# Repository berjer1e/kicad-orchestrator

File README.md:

# KiCad Orchestrator — 100% AI-Generated Hardware Design & Verification Suite

> [!IMPORTANT]
> **🇺🇦 Повністю згенерований ШІ-інструмент / 🇬🇧 100% AI-Generated Tool**
>
> **Українською:** Весь цей репозиторій — **14-інструментний MCP-сервер для KiCad 10**, **5-агентний оркестратор-плагін (`v0.5.0`)** (разом із Design QA Gate та Gemini API делегатором) та **приклад проєкту друкованої плати калькулятора (`examples/calculator/`)** — є **повністю згенерованим ШІ інструментом (100% AI-Generated Hardware Design & Verification Suite)**. Перед виготовленням серійних плат обов'язково переглядайте Gerber, drill-файли та DRC-звіти.
>
> **English:** This entire repository — the **14-tool KiCad 10 MCP server**, the **5-agent orchestrator plugin (`v0.5.0`)**, and the **Calculator PCB reference project (`examples/calculator/`)** — is a **100% AI-Generated Tool**. Always review exported Gerbers, drill maps, and DRC reports prior to mass fabrication.

---

## Showcase: Calculator Reference Project (`examples/calculator/`)

The flagship hardware project in [`./examples/calculator/`](./examples/calculator/) is a complete KiCad 10 rechargeable desktop calculator board featuring:

- **MCU & Core:** `ATmega328P-AU` + `16 MHz` (`HC-49S`) crystal oscillator with `22 pF` load capacitors and `100 nF` decoupling
- **Display Mezzanine:** `LCD1602 I2C` interface (`J_LCD1` `JST-XH` / header architecture with mechanical & Z-clearance audit)
- **User Input:** `32-key 4x8` tactile switch matrix (`SW1..SW32`, `6x6 mm`) with `1N4148` anti-ghosting diodes (`D1..D32`)
- **Power & Charging:** `HW-373 TP4056` Li-ion USB Type-C charger (`U_CHG1`, `2.0 mm` edge overhang) + `MT3608` boost converter (`U_BOOST1`) + `J_BATT1` / `J_PWR_IN1` / `J_SW_PWR1` `JST-XH` connectors
- **PCB Stackup & Routing:** `130 x 90 mm` 2-layer `FR-4` (`1.6 mm`), explicit `GND` tracks + `B.Cu` ground zone pour (`Доріжки + Зона`), and `M3` (`H1..H4`) corner mounting holes

### 3D Top Render & 2D Copper/Zone Preview

| 3D Top View (`calculator_top.png`) | Multi-Layer SVG Preview (`calculator_preview.svg`) |
| :---: | :---: |
|  |  |

Full automated verification output for the Calculator board is saved in [`./examples/calculator/output/audit_report.json`](./examples/calculator/output/audit_report.json).

---

## Repository Structure

```text
kicad-orchestrator/
├── mcp_server/                 # FastMCP server + S-expression PCB inspector + editor + generators
│   ├── server.py               # 20 consolidated FastMCP tools + compact schema sync helper
│   ├── run_tool.py             # Direct CLI dispatcher, `--sync-schemas`, and `--save-state-summary`
│   ├── api_delegate.py         # Gemini Interactions & Antigravity SDK delegator (`gemini-3.5-flash-lite` .. `gemini-4-carbon`)
│   ├── cli_wrapper.py          # KiCad 10 `kicad-cli.exe` wrapper with isolated config & lock-safe staging
│   ├── pcb_inspector.py        # Balanced-paren S-expr parser, compact audit mode, IPC-2221, mezzanine & QA gate
│   ├── pcb_editor.py           # Safe S-expr layout editor, trace/via mutator & 2-layer A* autorouter
│   ├── requirements.txt        # Python dependencies (`mcp`, `pydantic`, `google-genai`, `google-antigravity`)
│   ├── generators/             # BOM parser & KiCad 10 footprint/symbol generators
│   │   ├── __init__.py
│   │   ├── bom_parser.py
│   │   ├── footprint_gen.py
│   │   ├── symbol_gen.py
│   │   └── templates.py
│   └── schemas/                # 14 exported compact JSON tool schemas (`parameters.type == "object"`)
├── plugin/                     # Antigravity plugin bundle (`v0.5.0`)
│   ├── plugin.json
│   ├── mcp_config.json
│   ├── assets/logo.svg
│   └── skills/
│       ├── kicad-orchestrator/SKILL.md
│       ├── kicad-searcher/SKILL.md
│       ├── kicad-generator/SKILL.md
│       ├── kicad-tracer/SKILL.md
│       └── kicad-tester-converter/SKILL.md
├── examples/calculator/        # Complete Calculator KiCad 10 project + `Items.DOCX` + exports
├── LICENSE                     # MIT License (Copyright 2026 berjer1e)
└── README.md
```

---

## Architecture: 14 Consolidated MCP Tools (`v0.5.0`)

All 20 consolidated tools are exposed via FastMCP (`mcp_server/server.py`) with compact 1-sentence schema descriptions (`mcp_server/schemas/*.json`), compact/failures-first inspection defaults (`inspect_pcb_layout(compact=True)`), one-shot disk caching (`run_tool.py --save-state-summary`), deterministic schematic/netlist/PCB generation (`create_schematic`, `run_electrical_pipeline`), electrical netlist preparation (`create_netlist_from_bom`, `apply_netlist_to_pcb`, `add_nets_to_pcb`, `assign_pad_nets`), and optional Gemini SDK subtask delegation (`mcp_server/api_delegate.py`).

### 0. Safe S-Expression PCB Editing & 2-Layer A* Autorouting (`pcb_editor.py`)
| Tool | Key Parameters | Purpose |
| :--- | :--- | :--- |
| `edit_pcb_layout` | `pcb_path`, `board_outline=None`, `footprint_placements=None`, `zones=None`, `output_path=None` | Safely updates `Edge.Cuts` (rectangular or rounded corners), moves/rotates footprints by reference designator, and creates copper `(zone ...)` blocks without `pcbnew` SWIG/wxWidgets assertions. |
| `edit_pcb_traces` | `pcb_path`, `add_segments=None`, `add_vias=None`, `clear_nets=None`, `clear_bbox=None`, `output_path=None` | Adds or clears copper `(segment ...)` and `(via ...)` items with validated integer net IDs (resolving human net names automatically so `kicad-cli` never hangs on string net names). |
| `autoroute_pcb_nets` | `pcb_path`, `nets=None`, `grid_step_mm=0.5`, `trace_width_mm=0.3`, `clearance_mm=0.25`, `allow_vias=True`, `output_path=None` | Built-in obstacle-aware 2-layer 45°/orthogonal A* grid router directly over `.kicad_pcb` S-expressions for unrouted nets. |

### 1. S-Expression PCB Inspection & IPC-2221 Audit
| Tool | Key Parameters | Purpose |
| :--- | :--- | :--- |
| `inspect_pcb_layout` | `pcb_path` | Parses `Edge.Cuts` bounds, `board_stackup`, `silkscreen_audit` (font sizes, pad overlaps, connector pin labels), footprint bboxes, `estimated_height_mm`, track/via/zone stats, and lock status. |
| `find_unrouted_pads` | `pcb_path`, `net_filter=None`, `tolerance_mm=0.05` | Detects pads on multi-pad nets missing explicit copper `segment` tracks, separating `zone_only_pads` (e.g. `GND` relying only on zone pours) from `completely_unrouted_pads`. |
| `analyze_pcb_traces` | `pcb_path`, `net_currents_a=None`, `copper_oz=1.0`, `max_temp_rise_c=10.0`, `max_voltage_drop_v=0.1`, `neckdown_max_length_mm=3.0` | Computes IPC-2221 minimum trace widths, classifies pad-entry neck-downs (`trunk_ok`, `valid_neckdown`, `undersized_segment`), calculates segment resistance & `ΔU = I·R`, and audits critical net lengths (crystal `<= 15 mm`, `100 nF` decoupling `<= 8 mm`, `I2C`). |
| `manage_design_decisions` | `project_dir`, `action="check"`, `decisions=None`, `bom_or_pcb_path=None` | Checks, loads, or saves `<project_dir>/design_decisions.json` across the 8 Step 1.5 Design QA Gate categories. |

### 2. Mezzanine & 3D Mechanical Fit
| Tool | Key Parameters | Purpose |
| :--- | :--- | :--- |
| `check_mechanical_fit` | `pcb_path`, `min_clearance_mm=0.5`, `connector_clearance_mm=2.0`, `standoff_keepout_dia_mm=6.5`, `standoff_height_mm=10.0`, `mezzanine_modules=None` | Runs Checks A–E: same-side courtyard collisions, edge overhangs, connector mating clearances (`>= 2.0 mm`), mounting hole & display notes, standoff/screw-head keepouts (`M2.5 >= 5.5 mm`, `M3 >= 6.5 mm`), 2D projection + 3D Z-clearance (`estimated_height_mm`), and rigid board-to-board header alignment. |

### 3. Lock-Safe Zone Refill & DRC / ERC
| Tool | Key Parameters | Purpose |
| :--- | :--- | :--- |
| `refill_pcb_zones` | `pcb_path`, `output_path=None`, `force_when_locked=False` | Refills copper zones via `kicad-cli` in-place, or stages to `output_path` / `<stem>_refilled.kicad_pcb` when locked. |
| `run_validations` | `target_path=""`, `validation_type="drc"`, `output_path=None`, `schematic_parity=True`, `refill_zones=True`, `save_board=False` | Consolidated validation entrypoint (`drc` with `--schematic-parity`, `erc`, `footprint`/`symbol` SVG check, `locks` check, or `version`). |

### 4. Module Footprint/Symbol Generators & BOM Parser
| Tool | Key Parameters | Purpose |
| :--- | :--- | :--- |
| `parse_bom` | `source` | Parses Ukrainian/English BOM specs (`.txt`, `.csv`, or prose extracted from `.docx` such as `Items.DOCX`) into components, `board_properties`, `connector_details` (orientation, mounting, pitch, keying, current rating), pinouts, and rules. |
| `list_modules` | *(none)* | Lists built-in parametric module templates (`Mini360`, `Mini560`, `MT3608`, `TP4056_HW373`) and supported overrides. |
| `generate_module` | `module_name`, `output_dir`, `kind="both"`, `overrides=None` | Generates KiCad 10 `.kicad_mod` (`version 20260206`) footprints and/or `.kicad_sym` (`version 20251024`) symbols with keepouts and 100-mil pins. |

### 5. Manufacturing Exports & Environment
| Tool | Key Parameters | Purpose |
| :--- | :--- | :--- |
| `export_project` | `target_path`, `output_path`, `export_type="pcb_svg"`, `layers=None`, `width=1600`, `height=900`, `side="top"`, `quality="basic"`, `refill_zones=True` | Consolidated export tool supporting `gerbers`, `drill`, `step`, `sch_pdf`, `pcb_svg`, and `3d` PNG/JPEG renders (auto-stages zone refill if locked). |

---

## Architecture: 5 Autonomous Agent Skills & Step 1.5 Design QA Gate

The [`plugin/`](./plugin/) bundle (`v0.3.0`) coordinates five specialized agents:

1. **`kicad-orchestrator`** — Master coordinator executing the 6-stage pipeline:
   - **Step 1 (Ingest & Pre-Flight):** Runs `parse_bom` (`board_properties`, `connector_details`), `run_validations(..., validation_type="locks")`, and caches compact PCB state (`--save-state-summary`) to `output/state_summary.json`.
   - **Step 1.5 (Design QA Gate):** Calls `manage_design_decisions(project_dir, action="check")` and interactively resolves any ambiguities with the user via `ask_question` / `/grill-me`, persisting answers into `<project_dir>/design_decisions.json` across **8 mandatory categories**:
     1. `display_mounting_mode` (`panel_cable` vs `pcb_mezzanine`)
     2. `module_variants` (e.g. `Mini560` SMD `15x18` vs THT `29x18`)
     3. `connector_orientation_and_keying` (`vertical` vs `right_angle`, `keyed` vs unkeyed)
     4. `button_interface` (on-board `6x6` tactile switches vs external panel buttons)
     5. `pcb_stackup_and_limits` (`layer_count`, `copper_oz` `1.0`/`2.0`, `board_thickness_mm`)
     6. `board_shape_and_mounting` (`M2.5`/`M3` holes, `5.5`/`6.5 mm` standoff keepouts, `R3` corners)
     7. `silkscreen_conventions` (functional designators like `U_CHG1`, pin/polarity labels)
     8. `enclosure_fit_and_overhangs` (USB Type-C overhang, max component Z-height)
   - **Step 2 (Discovery & Generation):** Dispatches `searcher` and `generator`.
   - **Step 3 (Routing & Mechanical Audit):** Dispatches `tracer`.
   - **Step 4 (Verification & Export):** Dispatches `tester-converter`.
   - **Step 5 (Final Report):** Summarizes verified artifacts, metrics, and warnings.
2. **`kicad-searcher`** — Verifies KiCad 10 standard library mappings, module dimensions, connector orientation/mounting/pitch/keying, 3D Z-heights (`estimated_height_mm`), and mezzanine `(dx, dy)` hole-to-header offsets.
3. **`kicad-generator`** — Loads `design_decisions.json`, consumes `board_properties` & `connector_details`, and builds `.kicad_mod`/`.kicad_sym` files with standoff keepouts, keyed pin-1 markers, and `>= 1.0 x 0.15 mm` silkscreen labels.
4. **`kicad-tracer`** — Enforces IPC-2221 trace widths with pad-aware neck-down (`<= 3.0 mm`) & `ΔU = I·R <= 0.1 V`, explicit `GND` tracks + copper zone ("Доріжки + Зона"), silkscreen polarity traceability, and the 3 stacked/mezzanine checks.
5. **`kicad-tester-converter`** — Runs the full verification and export suite (`run_validations` for `locks`/`erc`/`drc`, `inspect_pcb_layout`, `analyze_pcb_traces`, `find_unrouted_pads`, `check_mechanical_fit`, `refill_pcb_zones`, and `export_project` for Gerber/Drill/STEP/SVG/PDF/3D outputs).

---

## Quick Start (Windows / KiCad 10)

### 1. Prerequisites
- **KiCad 10.0+** installed (the `kicad-cli` executable available on your PATH)
- **Python 3.11+**

### Host Integration

The repository is split into a client-independent MCP backend and host-specific prompt
adapters. Read [`AGENTS.md`](./AGENTS.md) first. Antigravity can load the native `swarm`
Skill; OpenCode, Codex, and Claude Code can use the files under [`adapters/`](./adapters/).
When a host cannot create subagents, use the deterministic fallback:

```powershell
python mcp_server/doctor.py --json
python mcp_server/run_tool.py run_electrical_pipeline --args '{\"pcb_path\":\"path\\to\\board.kicad_pcb\"}'
```

Subagent availability is controlled by the host, quota, and permissions. MCP itself does not
spawn workers, so every workflow has a single-agent fallback.

### 2. Set Up the MCP Server Virtual Environment
```powershell
git clone https://github.com/berjer1e/kicad-orchestrator.git
cd kicad-orchestrator\mcp_server

python -m venv .venv
.\.venv\Scripts\Activate.ps1
pip install -r requirements.txt
```

### 3. Configure & Install the Antigravity Plugin
1. Update `plugin\mcp_config.json` paths (`command`, `args`, `KICAD_MCP_ROOT`, `KICAD_MCP_PYTHON`, and `KICAD_CLI_PATH`) to match your cloned `kicad-orchestrator\mcp_server\` directory.
2. Copy `plugin\` to `%USERPROFILE%\.gemini\config\plugins\kicad-orchestrator\`.
3. Sync the 22 JSON tool schemas:
```powershell
.\.venv\Scripts\python.exe run_tool.py --sync-schemas
```

### 4. Run Any Tool Directly via CLI (`run_tool.py`)
```powershell
# Check KiCad CLI version & GUI locks
.\.venv\Scripts\python.exe run_tool.py run_validations --args '{\"target_path\": \"..\\examples\\calculator\\Calculator.kicad_pcb\", \"validation_type\": \"version\"}'

# Cache compact PCB layout/trace/unrouted/fit state to disk once for zero-MCP agents
.\.venv\Scripts\python.exe run_tool.py --save-state-summary ..\examples\calculator\Calculator.kicad_pcb ..\examples\calculator\output\state_summary.json

# Run compact inspection, IPC-2221 trace analysis, schematic-parity DRC & SVG export
.\.venv\Scripts\python.exe run_tool.py inspect_pcb_layout --args '{\"pcb_path\": \"..\\examples\\calculator\\Calculator.kicad_pcb\"}'
.\.venv\Scripts\python.exe run_tool.py analyze_pcb_traces --args '{\"pcb_path\": \"..\\examples\\calculator\\Calculator.kicad_pcb\"}'
.\.venv\Scripts\python.exe run_tool.py run_validations --args '{\"target_path\": \"..\\examples\\calculator\\Calculator.kicad_pcb\", \"validation_type\": \"drc\", \"schematic_parity\": true}'

# Delegate lightweight BOM/spec reasoning via Gemini Interactions API
.\.venv\Scripts\python.exe api_delegate.py --list-models
```

---

## License

- **mcp_server/ (MCP Engine & Tools):** Licensed under the [GNU AGPLv3](./LICENSE) (commercial licensing available upon request).
- **plugin/ & dapters/ (Agent Skills & Prompts):** Available under the [MIT License](./plugin/LICENSE).
- Last full-repository MIT snapshot is tagged as 0.6.0-mit — Copyright (c) 2026 erjer1e.

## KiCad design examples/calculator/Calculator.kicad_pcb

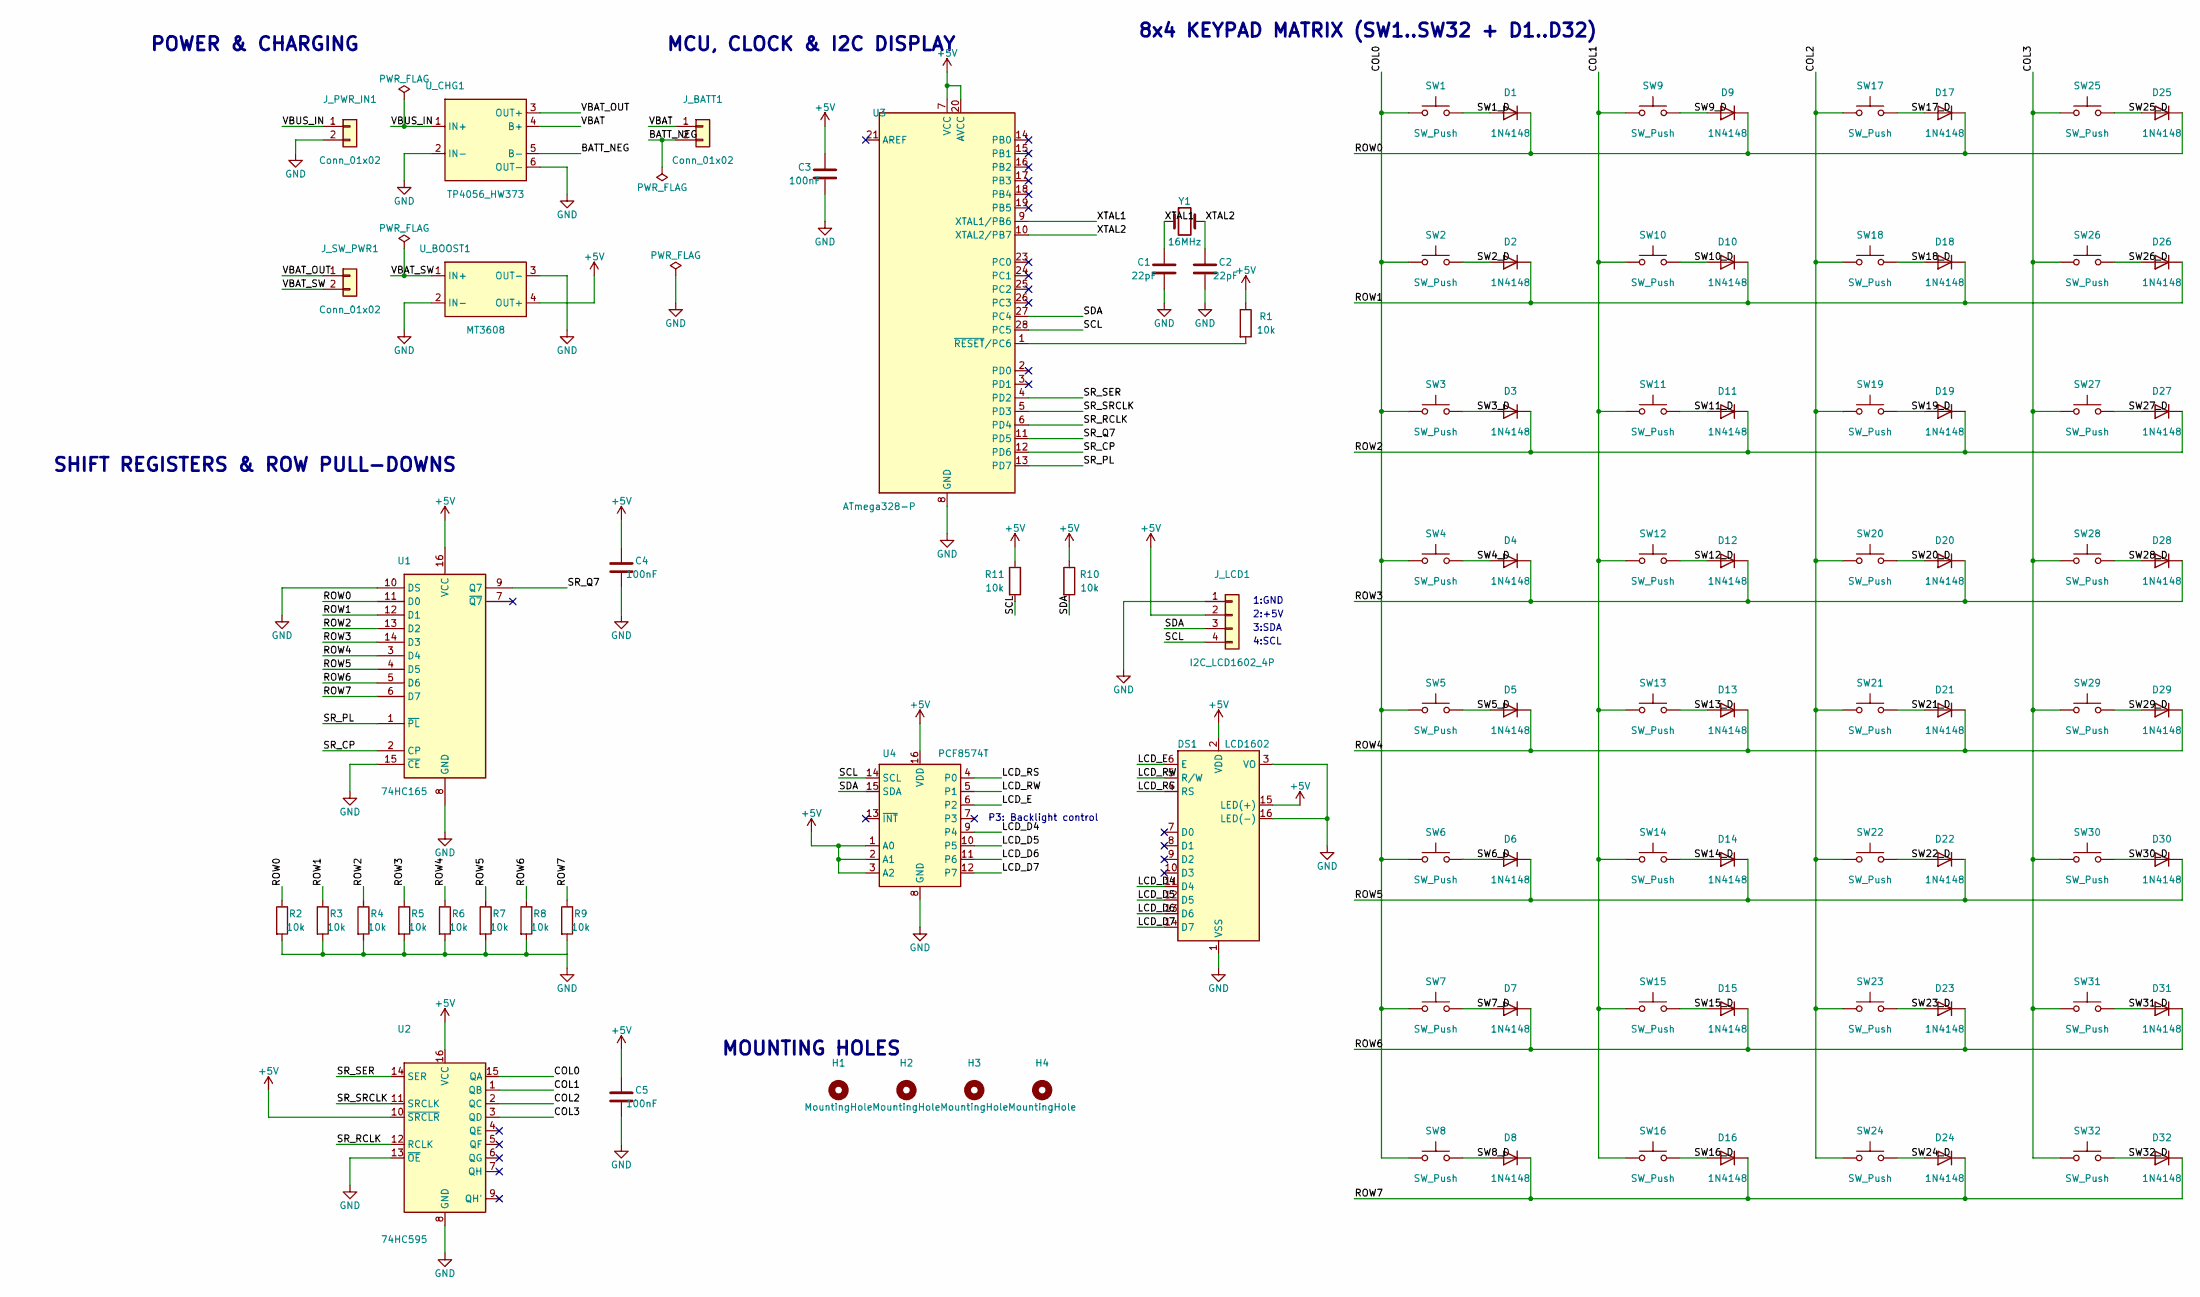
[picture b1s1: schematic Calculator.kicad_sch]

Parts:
C1, C2: 22pF; C_Disc_D5.0mm_W2.5mm_P2.50mm
C3, C4, C5: 100nF; C_Disc_D5.0mm_W2.5mm_P5.00mm
D1, D2, D3, D4, D5, D6, D7, D8, D9, D10, D11, D12, D13, D14, D15, D16, D17, D18, D19, D20, D21, D22, D23, D24, D25, D26, D27, D28, D29, D30, D31, D32: 1N4148; D_DO-35_SOD27_P2.54mm_Vertical_AnodeUp
DS1: LCD1602; WC1602A
H1, H2, H3, H4: MountingHole; MountingHole_3.2mm_M3
J_BATT1: Conn_01x02; JST_XH_B2B-XH-A_1x02_P2.50mm_Vertical
J_LCD1: I2C_LCD1602_4P; JST_XH_B4B-XH-A_1x04_P2.50mm_Vertical
J_PWR_IN1: Conn_01x02; JST_XH_B2B-XH-A_1x02_P2.50mm_Vertical
J_SW_PWR1: Conn_01x02; JST_XH_B2B-XH-A_1x02_P2.50mm_Vertical
R1, R10, R11: 10k; R_Axial_DIN0207_L6.3mm_D2.5mm_P2.54mm_Vertical
R2, R3, R4, R5, R6, R7, R8, R9: 10k; R_Axial_DIN0207_L6.3mm_D2.5mm_P7.62mm_Horizontal
SW1, SW2, SW3, SW4, SW5, SW6, SW7, SW8, SW9, SW10, SW11, SW12, SW13, SW14, SW15, SW16, SW17, SW18, SW19, SW20, SW21, SW22, SW23, SW24, SW25, SW26, SW27, SW28, SW29, SW30, SW31, SW32: SW_Push; SW_PUSH_6mm_H5mm
U1: 74HC165; DIP-16_W7.62mm_Socket
U2: 74HC595; DIP-16_W7.62mm_Socket
U3: ATmega328-P; DIP-28_W7.62mm_Socket
U4: PCF8574T; SOIC-16W_7.5x10.3mm_P1.27mm
U_BOOST1: MT3608
U_CHG1: TP4056_HW373
Y1: 16MHz; Crystal_HC49-4H_Vertical

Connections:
+5V: C3.1, C4.1, C5.1, DS1.2 (VDD), DS1.15 (LED(+)), J_LCD1.2, R1.1, R10.1, R11.1, U1.16 (VCC), U2.10 (~SRCLR), U2.16 (VCC), U3.7 (VCC), U3.20 (AVCC), U4.1 (A0), U4.2 (A1), U4.3 (A2), U4.16 (VDD), U_BOOST1.4 (OUT+)
/BATT_NEG: J_BATT1.2, U_CHG1.5 (B-)
/COL0: SW1.1, SW2.1, SW3.1, SW4.1, SW5.1, SW6.1, SW7.1, SW8.1, U2.15 (QA)
/COL1: SW9.1, SW10.1, SW11.1, SW12.1, SW13.1, SW14.1, SW15.1, SW16.1, U2.1 (QB)
/COL2: SW17.1, SW18.1, SW19.1, SW20.1, SW21.1, SW22.1, SW23.1, SW24.1, U2.2 (QC)
/COL3: SW25.1, SW26.1, SW27.1, SW28.1, SW29.1, SW30.1, SW31.1, SW32.1, U2.3 (QD)
/ROW0: D1.1 (K), D9.1 (K), D17.1 (K), D25.1 (K), R2.1, U1.11 (D0)
/ROW1: D2.1 (K), D10.1 (K), D18.1 (K), D26.1 (K), R3.1, U1.12 (D1)
/ROW2: D3.1 (K), D11.1 (K), D19.1 (K), D27.1 (K), R4.1, U1.13 (D2)
/ROW3: D4.1 (K), D12.1 (K), D20.1 (K), D28.1 (K), R5.1, U1.14 (D3)
/ROW4: D5.1 (K), D13.1 (K), D21.1 (K), D29.1 (K), R6.1, U1.3 (D4)
/ROW5: D6.1 (K), D14.1 (K), D22.1 (K), D30.1 (K), R7.1, U1.4 (D5)
/ROW6: D7.1 (K), D15.1 (K), D23.1 (K), D31.1 (K), R8.1, U1.5 (D6)
/ROW7: D8.1 (K), D16.1 (K), D24.1 (K), D32.1 (K), R9.1, U1.6 (D7)
/SCL: J_LCD1.4, R11.2, U3.28 (PC5), U4.14 (SCL)
/SDA: J_LCD1.3, R10.2, U3.27 (PC4), U4.15 (SDA)
/SR_CP: U1.2 (CP), U3.12 (PD6)
/SR_PL: U1.1 (~PL), U3.13 (PD7)
/SR_Q7: U1.9 (Q7), U3.11 (PD5)
/SR_RCLK: U2.12 (RCLK), U3.6 (PD4)
/SR_SER: U2.14 (SER), U3.4 (PD2)
/SR_SRCLK: U2.11 (SRCLK), U3.5 (PD3)
/SW1_D: D1.2 (A), SW1.2
/SW2_D: D2.2 (A), SW2.2
/SW3_D: D3.2 (A), SW3.2
/SW4_D: D4.2 (A), SW4.2
/SW5_D: D5.2 (A), SW5.2
/SW6_D: D6.2 (A), SW6.2
/SW7_D: D7.2 (A), SW7.2
/SW8_D: D8.2 (A), SW8.2
/SW9_D: D9.2 (A), SW9.2
/SW10_D: D10.2 (A), SW10.2
/SW11_D: D11.2 (A), SW11.2
/SW12_D: D12.2 (A), SW12.2
/SW13_D: D13.2 (A), SW13.2
/SW14_D: D14.2 (A), SW14.2
/SW15_D: D15.2 (A), SW15.2
/SW16_D: D16.2 (A), SW16.2
/SW17_D: D17.2 (A), SW17.2
/SW18_D: D18.2 (A), SW18.2
/SW19_D: D19.2 (A), SW19.2
/SW20_D: D20.2 (A), SW20.2
/SW21_D: D21.2 (A), SW21.2
/SW22_D: D22.2 (A), SW22.2
/SW23_D: D23.2 (A), SW23.2
/SW24_D: D24.2 (A), SW24.2
/SW25_D: D25.2 (A), SW25.2
/SW26_D: D26.2 (A), SW26.2
/SW27_D: D27.2 (A), SW27.2
/SW28_D: D28.2 (A), SW28.2
/SW29_D: D29.2 (A), SW29.2
/SW30_D: D30.2 (A), SW30.2
/SW31_D: D31.2 (A), SW31.2
/SW32_D: D32.2 (A), SW32.2
/VBAT: J_BATT1.1, U_CHG1.4 (B+)
/VBAT_OUT: J_SW_PWR1.1, U_CHG1.3 (OUT+)
/VBAT_SW: J_SW_PWR1.2, U_BOOST1.1 (IN+)
/VBUS_IN: J_PWR_IN1.1, U_CHG1.1 (IN+)
/XTAL1: C1.1, U3.9 (XTAL1/PB6), Y1.1
/XTAL2: C2.1, U3.10 (XTAL2/PB7), Y1.2
GND: C1.2, C2.2, C3.2, C4.2, C5.2, DS1.1 (VSS), DS1.3 (VO), DS1.16 (LED(-)), J_LCD1.1, J_PWR_IN1.2, R2.2, R3.2, R4.2, R5.2, R6.2, R7.2, R8.2, R9.2, U1.8 (GND), U1.10 (DS), U1.15 (~CE), U2.8 (GND), U2.13 (~OE), U3.8 (GND), U3.22 (GND), U4.8 (GND), U_BOOST1.2 (IN-), U_BOOST1.3 (OUT-), U_CHG1.2 (IN-), U_CHG1.6 (OUT-)
unnamed: DS1.4 (RS), U4.4 (P0)
unnamed: DS1.5 (R/W), U4.5 (P1)
unnamed: DS1.6 (E), U4.6 (P2)
unnamed: DS1.11 (D4), U4.9 (P4)
unnamed: DS1.12 (D5), U4.10 (P5)
unnamed: DS1.13 (D6), U4.11 (P6)
unnamed: DS1.14 (D7), U4.12 (P7)
unnamed: R1.2, U3.1 (~RESET/PC6)

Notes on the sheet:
POWER & CHARGING
SHIFT REGISTERS & ROW PULL-DOWNS
MCU, CLOCK & I2C DISPLAY
MOUNTING HOLES
8x4 KEYPAD MATRIX (SW1..SW32 + D1..D32)
1:GND
2:+5V
3:SDA
4:SCL
P3: Backlight control

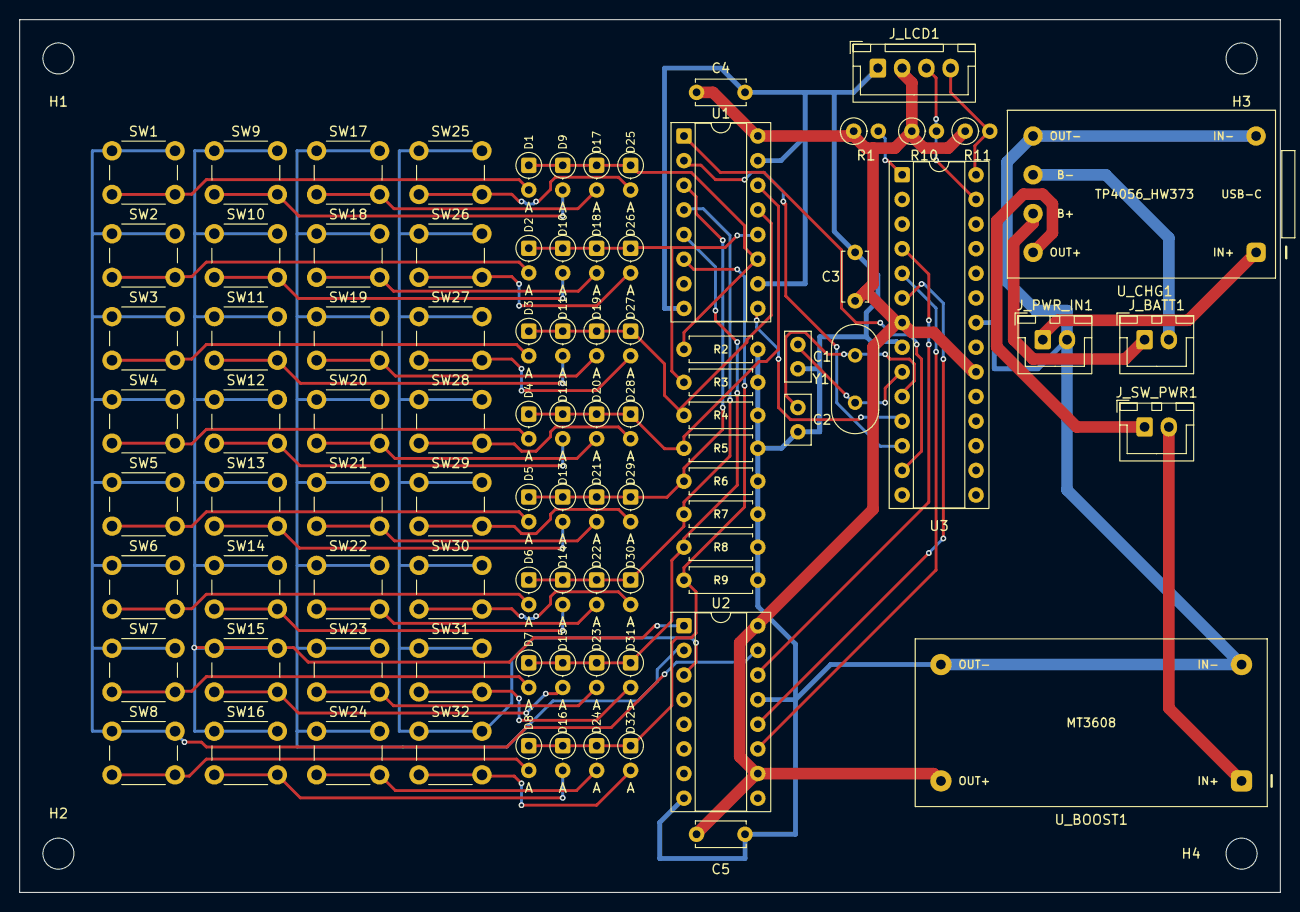
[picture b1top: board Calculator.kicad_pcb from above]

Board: 2 copper layers, 130.0 x 90.0 mm, 94 parts (0 on the bottom side), 62 nets.

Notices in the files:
README.md:
License: AGPL v3
